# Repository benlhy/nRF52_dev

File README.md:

# nRF52_dev
This Repo stores all folders for the nRF52832

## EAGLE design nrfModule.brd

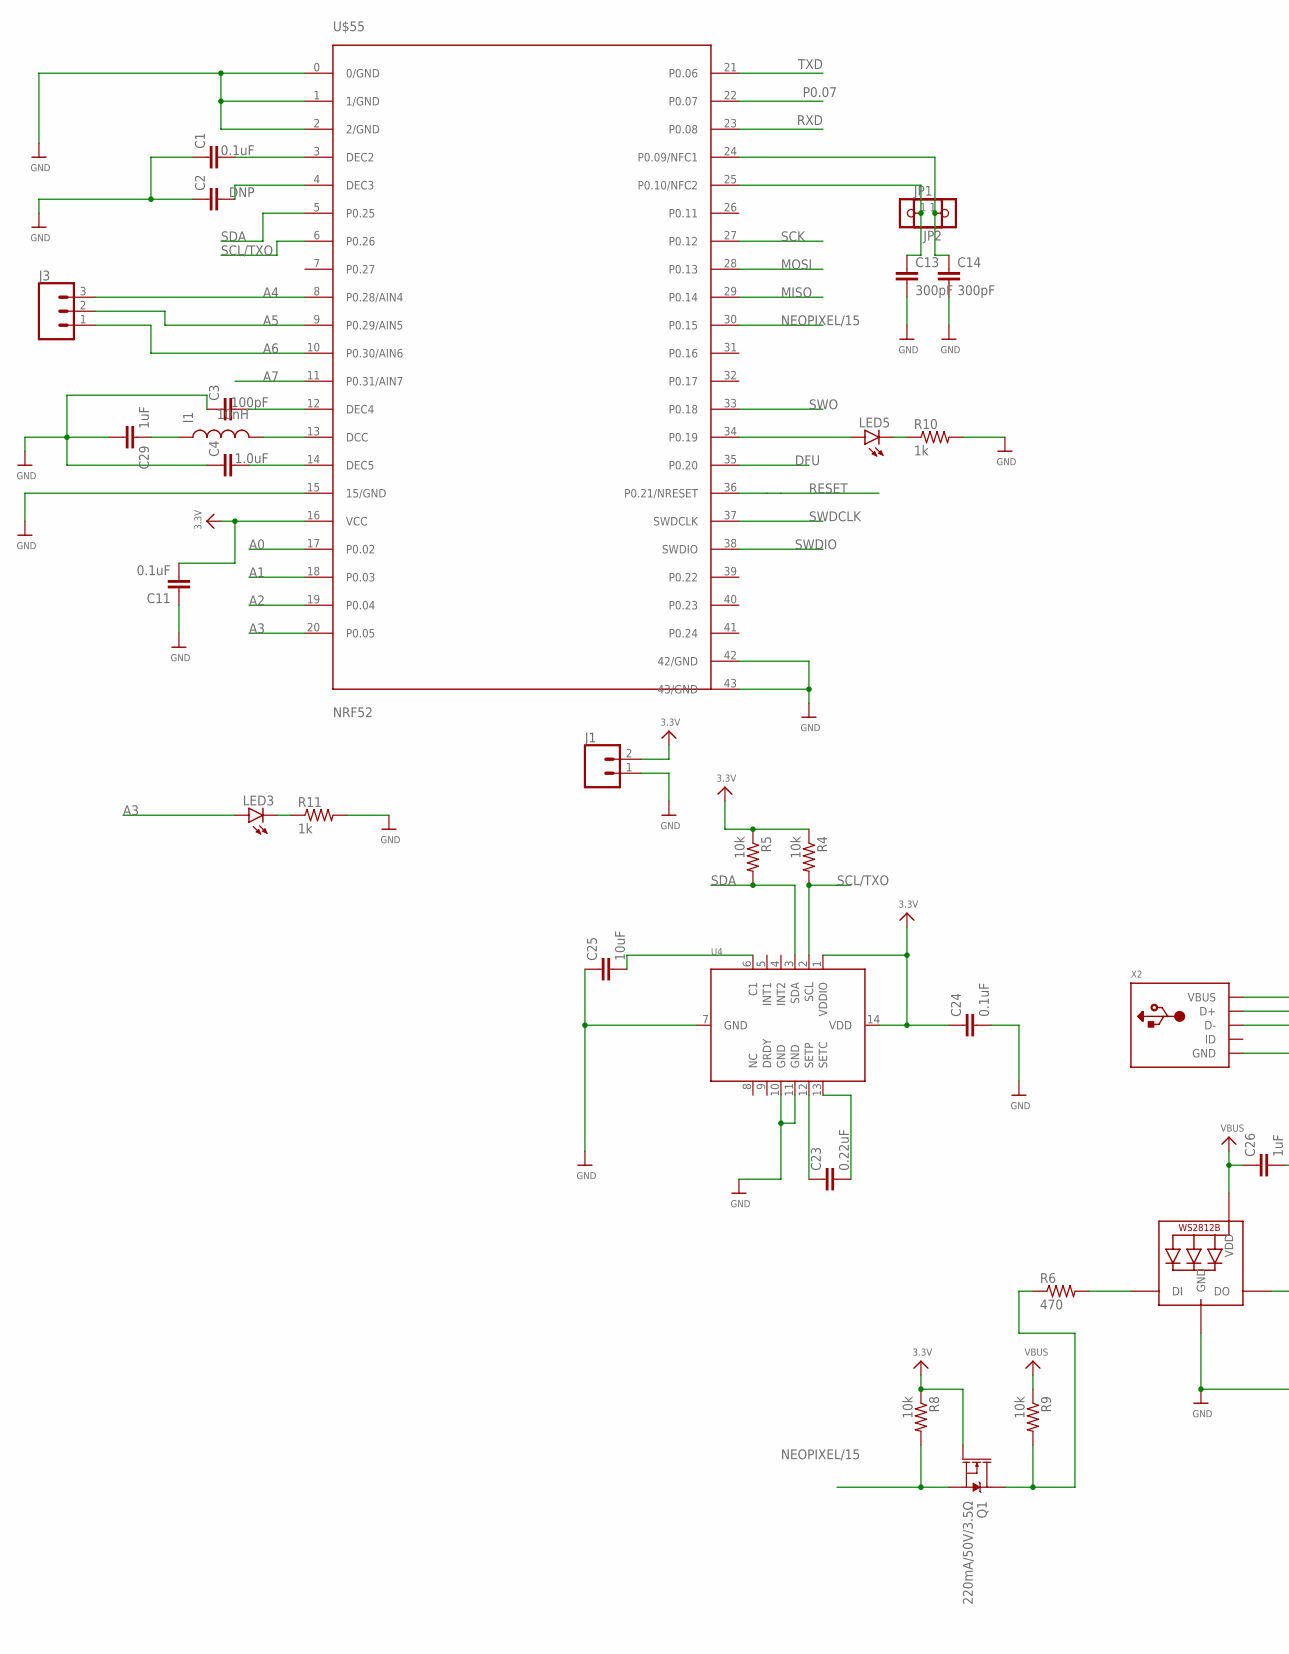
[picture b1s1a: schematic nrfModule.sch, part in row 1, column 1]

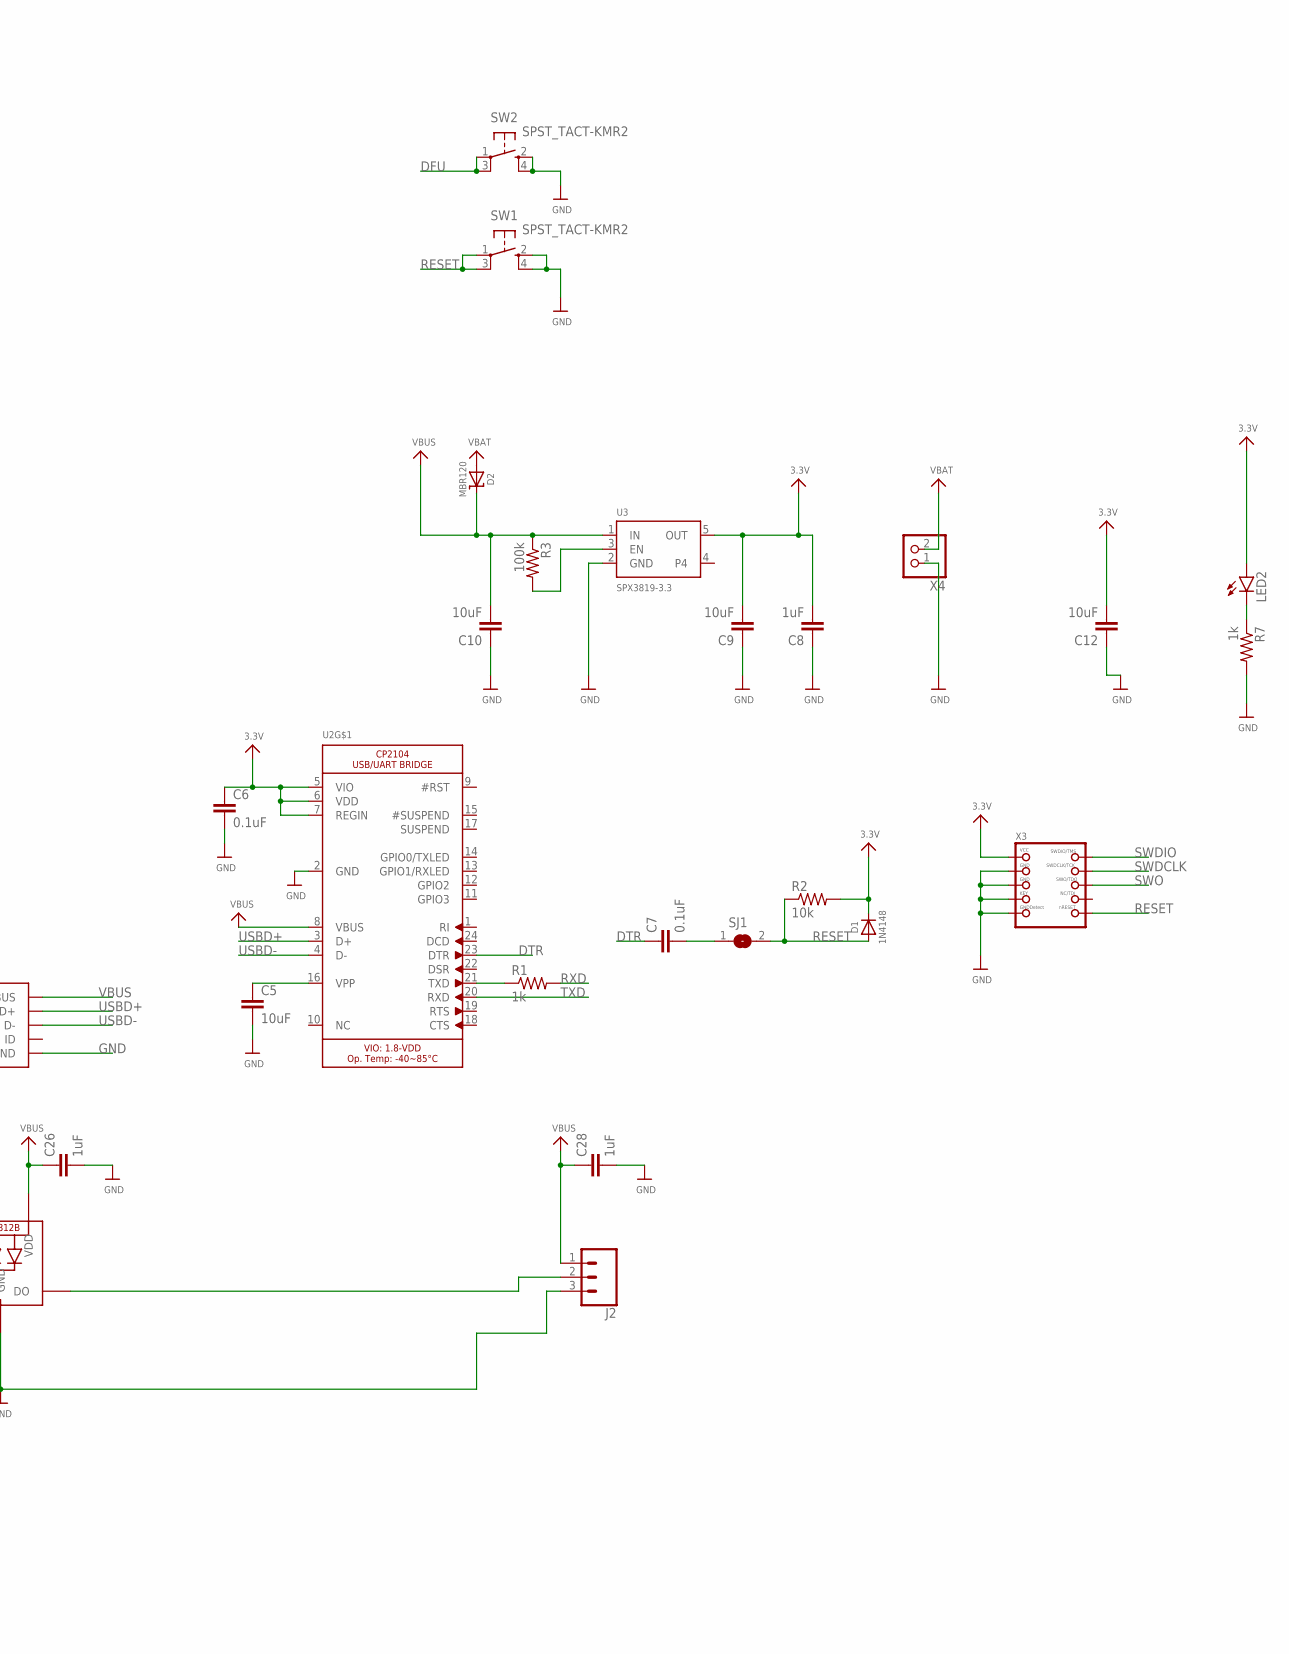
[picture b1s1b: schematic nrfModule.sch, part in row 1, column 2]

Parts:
C1, C6, C7, C11, C24: 0.1uF; 0805
C2: DNP; 0805
C3: 100pF; 0805
C4: 1.0uF; 0805
C5, C9, C10, C12, C25: 10uF; 0805
C8, C26, C28, C29: 1uF; 0805
C13, C14: 300pF; 0805
C23: 0.22uF; 0805
D1: 1N4148; SOD-323
D2: MBR120; SOD-123
I1: 10nH; 0805
J1: CONN_02; 1X02
J2, J3: CONN_03; 1X03
JP1, JP2: HEADER-1X12MM; 1X01_2MM
LED1: WS2812B5050; WS2812B
LED2, LED3, LED5: LED0603; LED-0603
Q1: 220mA/50V/3.5Ω; SOT23-3
R1, R7, R10, R11: 1k; 0805
R2, R4, R5, R8, R9: 10k; 0805
R3: 100k; 0805
R6: 470; 0805
SJ1: SOLDERJUMPERCLOSED; SOLDERJUMPER_CLOSEDWIRE
SW1, SW2: SPST_TACT-KMR2; KMR2
U2: CP2104; QFN24_4MM_SMSC
U3: SPX3819-3.3; SOT23-5
U4: LSM303DLHC; LGA14
U$55: NRF52
X2: USB_MICRO_20329_V2; 4UCONN_20329_V2
X3: JTAG-CORTEX; 2X05_1.27MM_SMT
X4: CON_JST_PH_2PIN; JSTPH2

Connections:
3.3V: C6.1, C8.2, C9.2, C11.2, C12.2, C24.1, D1.C, J1.2, LED2.A, Q1.1 (G), R2.2, R4.1, R5.1, R8.1, U2.5 (VIO), U2.6 (VDD), U2.7 (REGIN), U3.5 (OUT), U4.1 (VDDIO), U4.14 (VDD), U$55.16 (VCC), X3.1 (VCC)
A0: U$55.17 (P0.02)
A1: U$55.18 (P0.03)
A2: U$55.19 (P0.04)
A3: LED3.A, U$55.20 (P0.05)
A4: J3.3, U$55.8 (P0.28/AIN4)
A5: J3.2, U$55.9 (P0.29/AIN5)
A6: J3.1, U$55.10 (P0.30/AIN6)
A7: U$55.11 (P0.31/AIN7)
DFU: SW2.1, SW2.3 (P1), U$55.35 (P0.20)
DTR: C7.1, U2.23 (DTR)
GND: C1.1, C2.1, C3.1, C4.1, C5.2, C6.2, C8.1, C9.1, C10.1, C11.1, C12.1, C13.2, C14.2, C24.2, C25.1, C26.2, C28.2, C29.2, J1.1, J2.3, LED1.3-GND (GND), R7.2, R10.2, R11.2, SW1.2 (S), SW1.4 (S1), SW2.2 (S), SW2.4 (S1), U2.2 (GND), U3.2 (GND), U4.7 (GND), U4.10 (GND), U4.11 (GND), U$55.0 (0/GND), U$55.1 (1/GND), U$55.2 (2/GND), U$55.15 (15/GND), U$55.42 (42/GND), U$55.43 (43/GND), X2.BASE@1 (GND), X2.BASE@2 (GND), X2.GND, X2.SPRT@1 (GND), X2.SPRT@2 (GND), X2.SPRT@3 (GND), X2.SPRT@4 (GND), X3.3 (GND), X3.5 (GND), X3.7 (KEY), X3.9 (GNDDETECT), X4.1
MISO: U$55.29 (P0.14)
MOSI: U$55.28 (P0.13)
unnamed: LED5.A, U$55.34 (P0.19)
unnamed: LED5.C, R10.1
unnamed: C2.2, U$55.4 (DEC3)
unnamed: C4.2, U$55.14 (DEC5)
unnamed: R1.1, U2.21 (TXD)
unnamed: C1.2, U$55.3 (DEC2)
unnamed: C5.1, U2.16 (VPP)
unnamed: C23.2, U4.13 (SETC)
unnamed: C13.1, JP2.1, U$55.25 (P0.10/NFC2)
unnamed: C7.2, SJ1.1
unnamed: C23.1, U4.12 (SETP)
unnamed: R3.2, U3.3 (EN)
unnamed: C14.1, JP1.1, U$55.24 (P0.09/NFC1)
unnamed: LED2.C, R7.1
unnamed: LED3.C, R11.1
unnamed: Q1.3 (D), R6.1, R9.2
unnamed: C25.2, U4.6 (C1)
unnamed: J2.2, LED1.2-DOUT (DO)
unnamed: LED1.4-DIN (DI), R6.2
unnamed: I1.2, U$55.13 (DCC)
unnamed: C29.1, I1.1
unnamed: C3.2, U$55.12 (DEC4)
NEOPIXEL/15: Q1.2 (S), R8.2, U$55.30 (P0.15)
P0.07: U$55.22 (P0.07)
RESET: D1.A, R2.1, SJ1.2, SW1.1, SW1.3 (P1), U$55.36 (P0.21/NRESET), X3.10 (NRESET)
RXD: R1.2, U$55.23 (P0.08)
SCK: U$55.27 (P0.12)
SCL/TXO: R4.2, U4.2 (SCL), U$55.6 (P0.26)
SDA: R5.2, U4.3 (SDA), U$55.5 (P0.25)
SWDCLK: U$55.37 (SWDCLK), X3.4 (SWDCLK)
SWDIO: U$55.38 (SWDIO), X3.2 (SWDIO)
SWO: U$55.33 (P0.18), X3.6 (SWO)
TP: U2.THERM (TP)
TXD: U2.20 (RXD), U$55.21 (P0.06)
USBD+: U2.3 (D+), X2.D+
USBD-: U2.4 (D-), X2.D-
VBAT: D2.A, X4.2
VBUS: C10.2, C26.1, C28.1, D2.C, J2.1, LED1.1-VDD (VDD), R3.1, R9.1, U2.8 (VBUS), U3.1 (IN), X2.VBUS

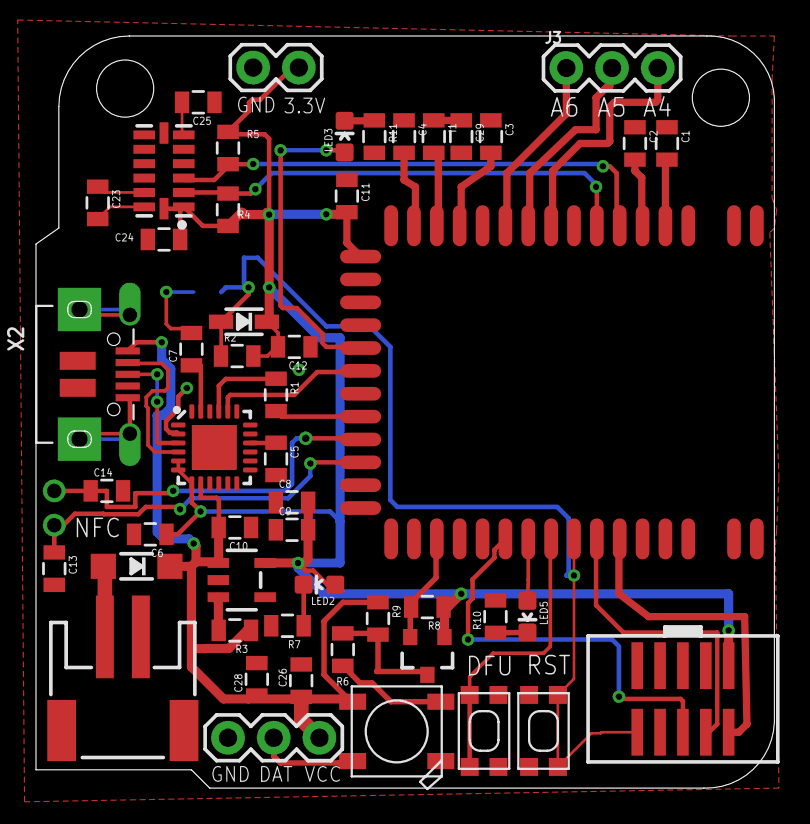
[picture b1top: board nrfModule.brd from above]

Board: 2 copper layers, 41.0 x 41.8 mm, 54 parts (1 on the bottom side), 43 nets.

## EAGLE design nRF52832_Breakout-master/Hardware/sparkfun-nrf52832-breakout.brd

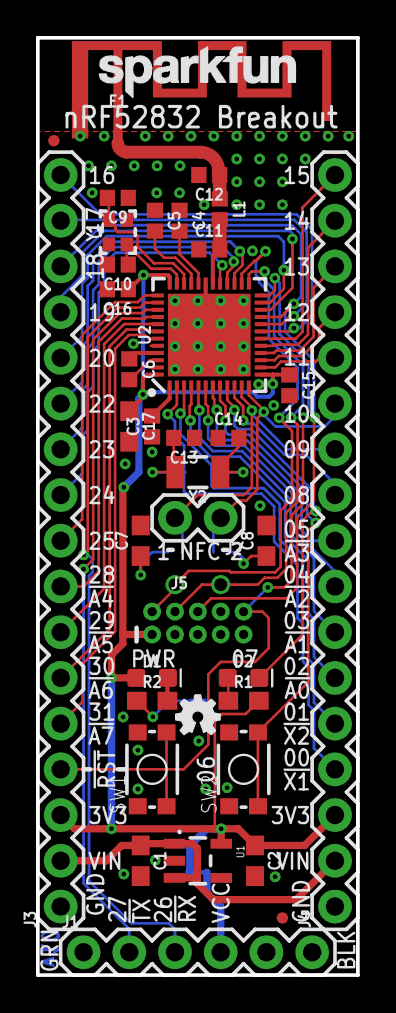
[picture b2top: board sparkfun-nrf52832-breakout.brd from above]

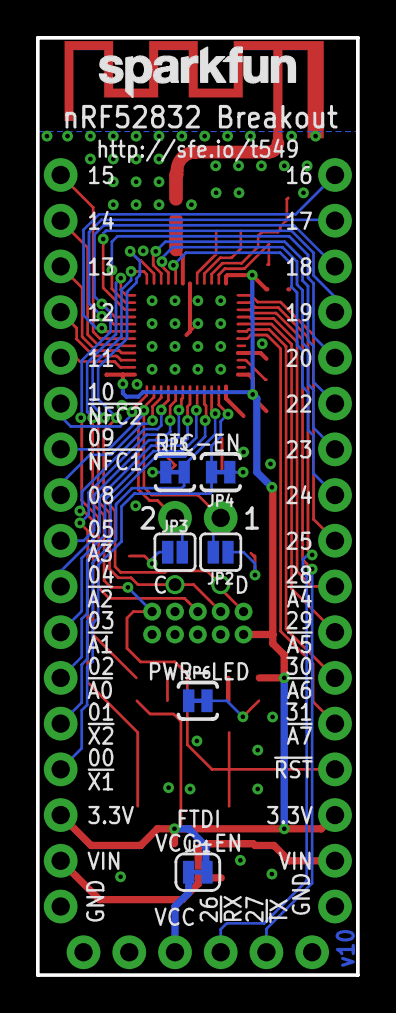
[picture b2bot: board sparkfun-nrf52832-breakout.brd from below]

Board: 2 copper layers, 17.8 x 52.1 mm, 48 parts (9 on the bottom side), 53 nets.

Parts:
C1: 1.0uF; 0603
C2: 2.2uF; 0603
C3, C15, C16: 0.1uF; 0402
C4, C12: DNP; 0402
C5: 100pF; 0402
C6: 1.0uF; 0402
C7, C8: 180pF; 0603
C9, C10: 6pF; 0402
C11: 0.8pF; 0402
C13, C14: 15pF; 0402
C17: 4.7uF; 0603
D1: RED; LED-0603
D2: BLUE; LED-0603
E1: ANT; TRACE_ANTENNA_2.4GHZ_15.2MM
FD1, FD2: FIDUCIALUFIDUCIAL; FIDUCIAL-MICRO
FRAME1: FRAME-LETTER; CREATIVE_COMMONS
J1: 1X06
J2: 1X02
J3, J4: 1X17
J5: CORTEX_DEBUGPTH; 2X5-PTH-1.27MM
JP1: VDD-EN; SMT-JUMPER_2_NC_TRACE_SILK
JP2: NFC1; SMT-JUMPER_2_NO_SILK
JP3: NFC2; SMT-JUMPER_2_NO_SILK
JP4: XL1; PAD-JUMPER-2-NC_BY_TRACE_YES_SILK
JP5: XL2; PAD-JUMPER-2-NC_BY_TRACE_YES_SILK
JP6: PWR-LED; PAD-JUMPER-2-NC_BY_TRACE_YES_SILK
L1: 3.9nH; 0402
LOGO1: OSHW-LOGOMINI; OSHW-LOGO-MINI
LOGO2, LOGO3: SFE_LOGO_NAME.1_INCH; SFE_LOGO_NAME_.1
R1, R2: 1k; 0603
SW1, SW2: TACTILE_SWITCH_SMD_4_6X2_8MM; TACTILE_SWITCH_SMD_4.6X2.8MM
TP1, TP2: TEST-POINT3X4; PAD.03X.04
U1: AP2112K-3.3V; SOT23-5
U2: NRF52832; QFN48-6X6MM
Y1: 32MHz; CRYSTAL-SMD-2.0X1.6MM
Y2: 32.768kHz; CRYSTAL-SMD-3.2X1.5MM

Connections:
!RESET!: J3.4, J5.10, SW1.1, SW1.2, U2.24
ANT: C11.2, L1.2, U2.30
DEC1: C3.2, U2.1
DEC2: C4.2, U2.32
DEC3: C5.2, U2.33
DEC4: C6.2, U2.46
GND: C1.2, C2.2, C3.1, C4.1, C5.1, C6.1, C7.2, C8.2, C9.1, C10.2, C11.1, C12.2, C13.1, C14.1, C15.2, C16.2, C17.2, E1.GND, J1.6, J3.1, J4.1, J5.3, J5.5, J5.9, JP6.1, SW1.3, SW1.4, SW2.3, SW2.4, U1.2, U2.31, U2.45, U2.EP
unnamed: JP6.2, R2.1
unnamed: C13.2, JP4.1, Y2.P$2
unnamed: C14.2, JP5.1, Y2.P$1
unnamed: C12.1, E1.ANT, L1.1
unnamed: D1.C, R2.2
unnamed: J1.4, JP1.1
unnamed: D2.A, R1.1
NFC1: C7.1, JP2.1
NFC2: C8.1, JP3.1
P00: J4.4, JP4.2, U2.2
P01: J4.5, JP5.2, U2.3
P02: J4.6, U2.4
P03: J4.7, U2.5
P04: J4.8, U2.6
P05: J4.9, U2.7
P06: SW2.1, SW2.2, U2.8
P07: D2.C, U2.9
P08: J4.10, U2.10
P09: J2.2, J4.11, JP2.2, U2.11
P10: J2.1, J4.12, JP3.2, U2.12
P11: J4.13, U2.14
P12: J4.14, U2.15
P13: J4.15, U2.16
P14: J4.16, U2.17
P15: J4.17, U2.18
P16: J3.17, U2.19
P17: J3.16, U2.20
P18: J3.15, J5.6, U2.21
P19: J3.14, U2.22
P20: J3.13, U2.23
P22: J3.12, U2.27
P23: J3.11, U2.28
P24: J3.10, U2.29
P25: J3.9, U2.37
P26: J1.3, U2.38
P27: J1.2, U2.39
P28: J3.8, U2.40
P29: J3.7, U2.41
P30: J3.6, U2.42
P31: J3.5, U2.43
SWDCLK: J5.4, TP2.P$1, U2.25
SWDIO: J5.2, TP1.P$1, U2.26
VDD: C2.1, C15.1, C16.1, C17.1, D1.A, J3.3, J4.3, J5.1, JP1.2, R1.2, U1.5, U2.13, U2.36, U2.48
VIN: C1.1, J3.2, J4.2, U1.1, U1.3
XC1: C9.2, U2.34, Y1.3
XC2: C10.1, U2.35, Y1.1

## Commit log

2017-07-29 Move
2017-09-12 antenna
2017-09-22 module schematics

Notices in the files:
parts and their libraries:
SparkFun-Aesthetics: Licensing: Creative Commons ShareAlike 4.0 International - https://creativecommons.org/licenses/by-sa/4.0
SparkFun-Aesthetics: Released under the Creative Commons Attribution Share-Alike 4.0 License
SparkFun-Aesthetics: https://creativecommons.org/licenses/by-sa/4.0
